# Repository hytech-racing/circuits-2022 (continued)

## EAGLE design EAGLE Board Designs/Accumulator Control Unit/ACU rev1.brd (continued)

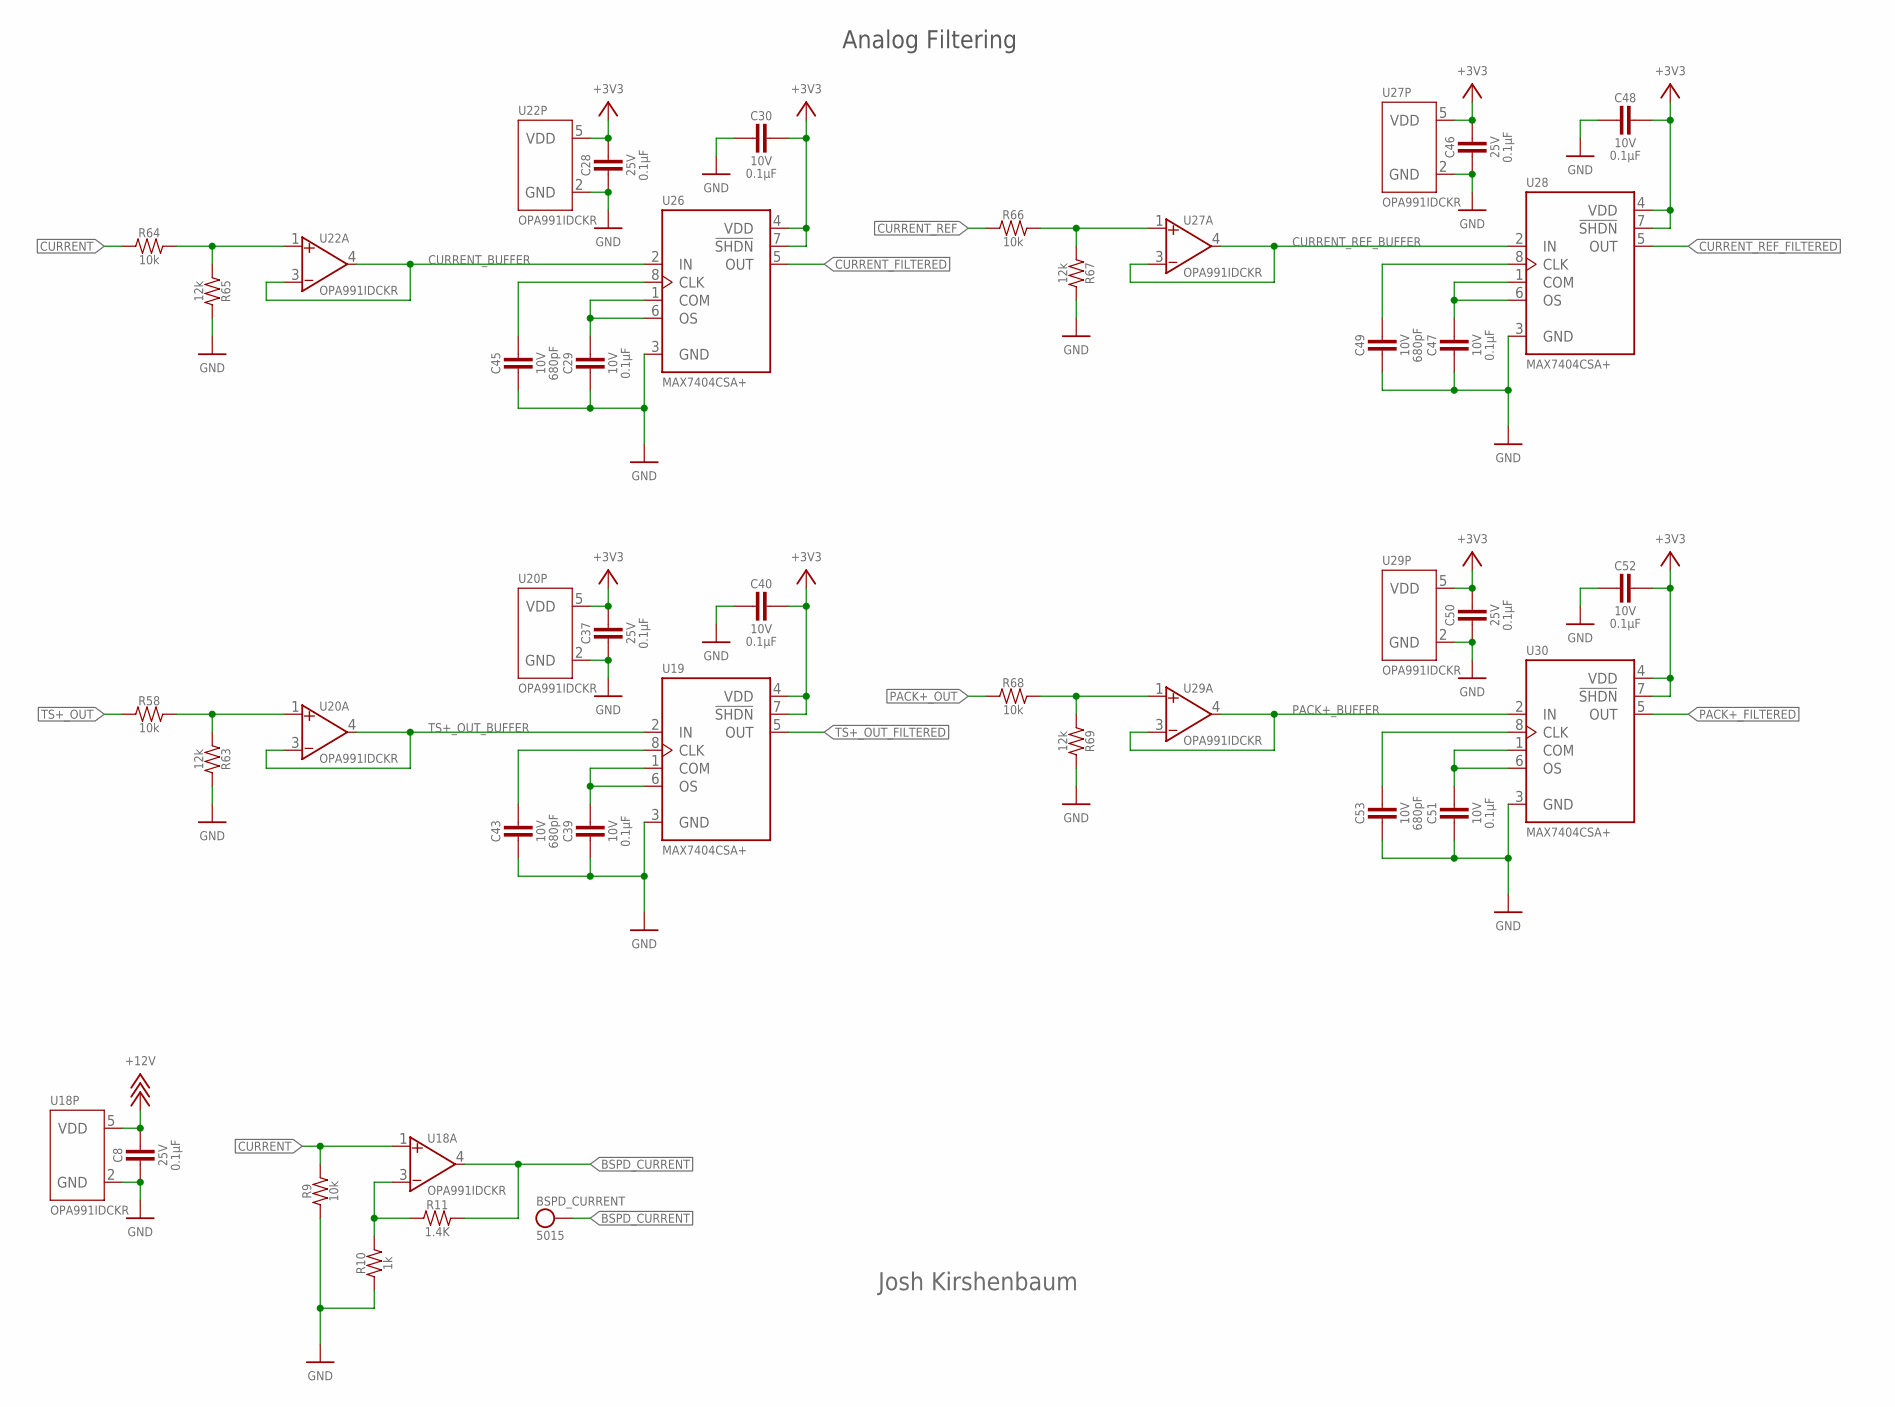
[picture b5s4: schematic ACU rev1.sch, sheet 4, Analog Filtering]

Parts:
BSPD_CURRENT: TEST_POINT; MICRO_MINIATURE
C8, C28, C37, C46, C50: CAPACITOR_0603_25V_0.1UF; 0603-CAP
C29, C30, C39, C40, C47, C48, C51, C52: CAPACITOR_0603_10V_0.1UF; 0603-CAP
C43, C45, C49, C53: CAPACITOR_0603_10V_680PF; 0603-CAP
R9, R58, R64, R66, R68: RESISTOR_0603_10K; 0603-RES
R10: RESISTOR_0603_1K; 0603-RES
R11: RESISTOR_0603_1.4K; 0603-RES
R63, R65, R67, R69: RESISTOR_0603_12K; 0603-RES
U18, U20, U22, U27, U29: OPAMP_1_CHANNEL_OPA991; SC-70-5
U19, U26, U28, U30: MAX7404; SOIC-08(NARROW,0.15")

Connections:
+3V3: C28.1, C30.1, C37.1, C40.1, C46.1, C48.1, C50.1, C52.1, U19.4 (VDD), U19.7 (!SHDN), U20.5 (VDD), U22.5 (VDD), U26.4 (VDD), U26.7 (!SHDN), U27.5 (VDD), U28.4 (VDD), U28.7 (!SHDN), U29.5 (VDD), U30.4 (VDD), U30.7 (!SHDN); also elsewhere on the board
+12V: C8.1, U18.5 (VDD); also elsewhere on the board
BSPD_CURRENT: BSPD_CURRENT.1, R11.2, U18.4 (VOUT); also elsewhere on the board
CURRENT: R9.2, R64.1, U18.1 (VIN+); also elsewhere on the board
CURRENT_BUFFER: U22.3 (VIN-), U22.4 (VOUT), U26.2 (IN)
CURRENT_FILTERED: U26.5 (OUT); also elsewhere on the board
CURRENT_REF: R66.1; also elsewhere on the board
CURRENT_REF_BUFFER: U27.3 (VIN-), U27.4 (VOUT), U28.2 (IN)
CURRENT_REF_FILTERED: U28.5 (OUT); also elsewhere on the board
GND: C8.2, C28.2, C29.2, C30.2, C37.2, C39.2, C40.2, C43.2, C45.2, C46.2, C47.2, C48.2, C49.2, C50.2, C51.2, C52.2, C53.2, R9.1, R10.1, R63.2, R65.2, R67.2, R69.2, U18.2 (GND), U19.3 (GND), U20.2 (GND), U22.2 (GND), U26.3 (GND), U27.2 (GND), U28.3 (GND), U29.2 (GND), U30.3 (GND); also elsewhere on the board
unnamed: R10.2, R11.1, U18.3 (VIN-)
unnamed: C39.1, U19.1 (COM), U19.6 (OS)
unnamed: C43.1, U19.8 (CLK)
unnamed: R58.2, R63.1, U20.1 (VIN+)
unnamed: C29.1, U26.1 (COM), U26.6 (OS)
unnamed: C45.1, U26.8 (CLK)
unnamed: R64.2, R65.1, U22.1 (VIN+)
unnamed: C47.1, U28.1 (COM), U28.6 (OS)
unnamed: C49.1, U28.8 (CLK)
unnamed: R66.2, R67.1, U27.1 (VIN+)
unnamed: C51.1, U30.1 (COM), U30.6 (OS)
unnamed: C53.1, U30.8 (CLK)
unnamed: R68.2, R69.1, U29.1 (VIN+)
PACK+_BUFFER: U29.3 (VIN-), U29.4 (VOUT), U30.2 (IN)
PACK+_FILTERED: U30.5 (OUT); also elsewhere on the board
PACK+_OUT: R68.1; also elsewhere on the board
TS+_OUT: R58.1; also elsewhere on the board
TS+_OUT_BUFFER: U19.2 (IN), U20.3 (VIN-), U20.4 (VOUT)
TS+_OUT_FILTERED: U19.5 (OUT); also elsewhere on the board

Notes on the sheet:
Josh Kirshenbaum
Analog Filtering

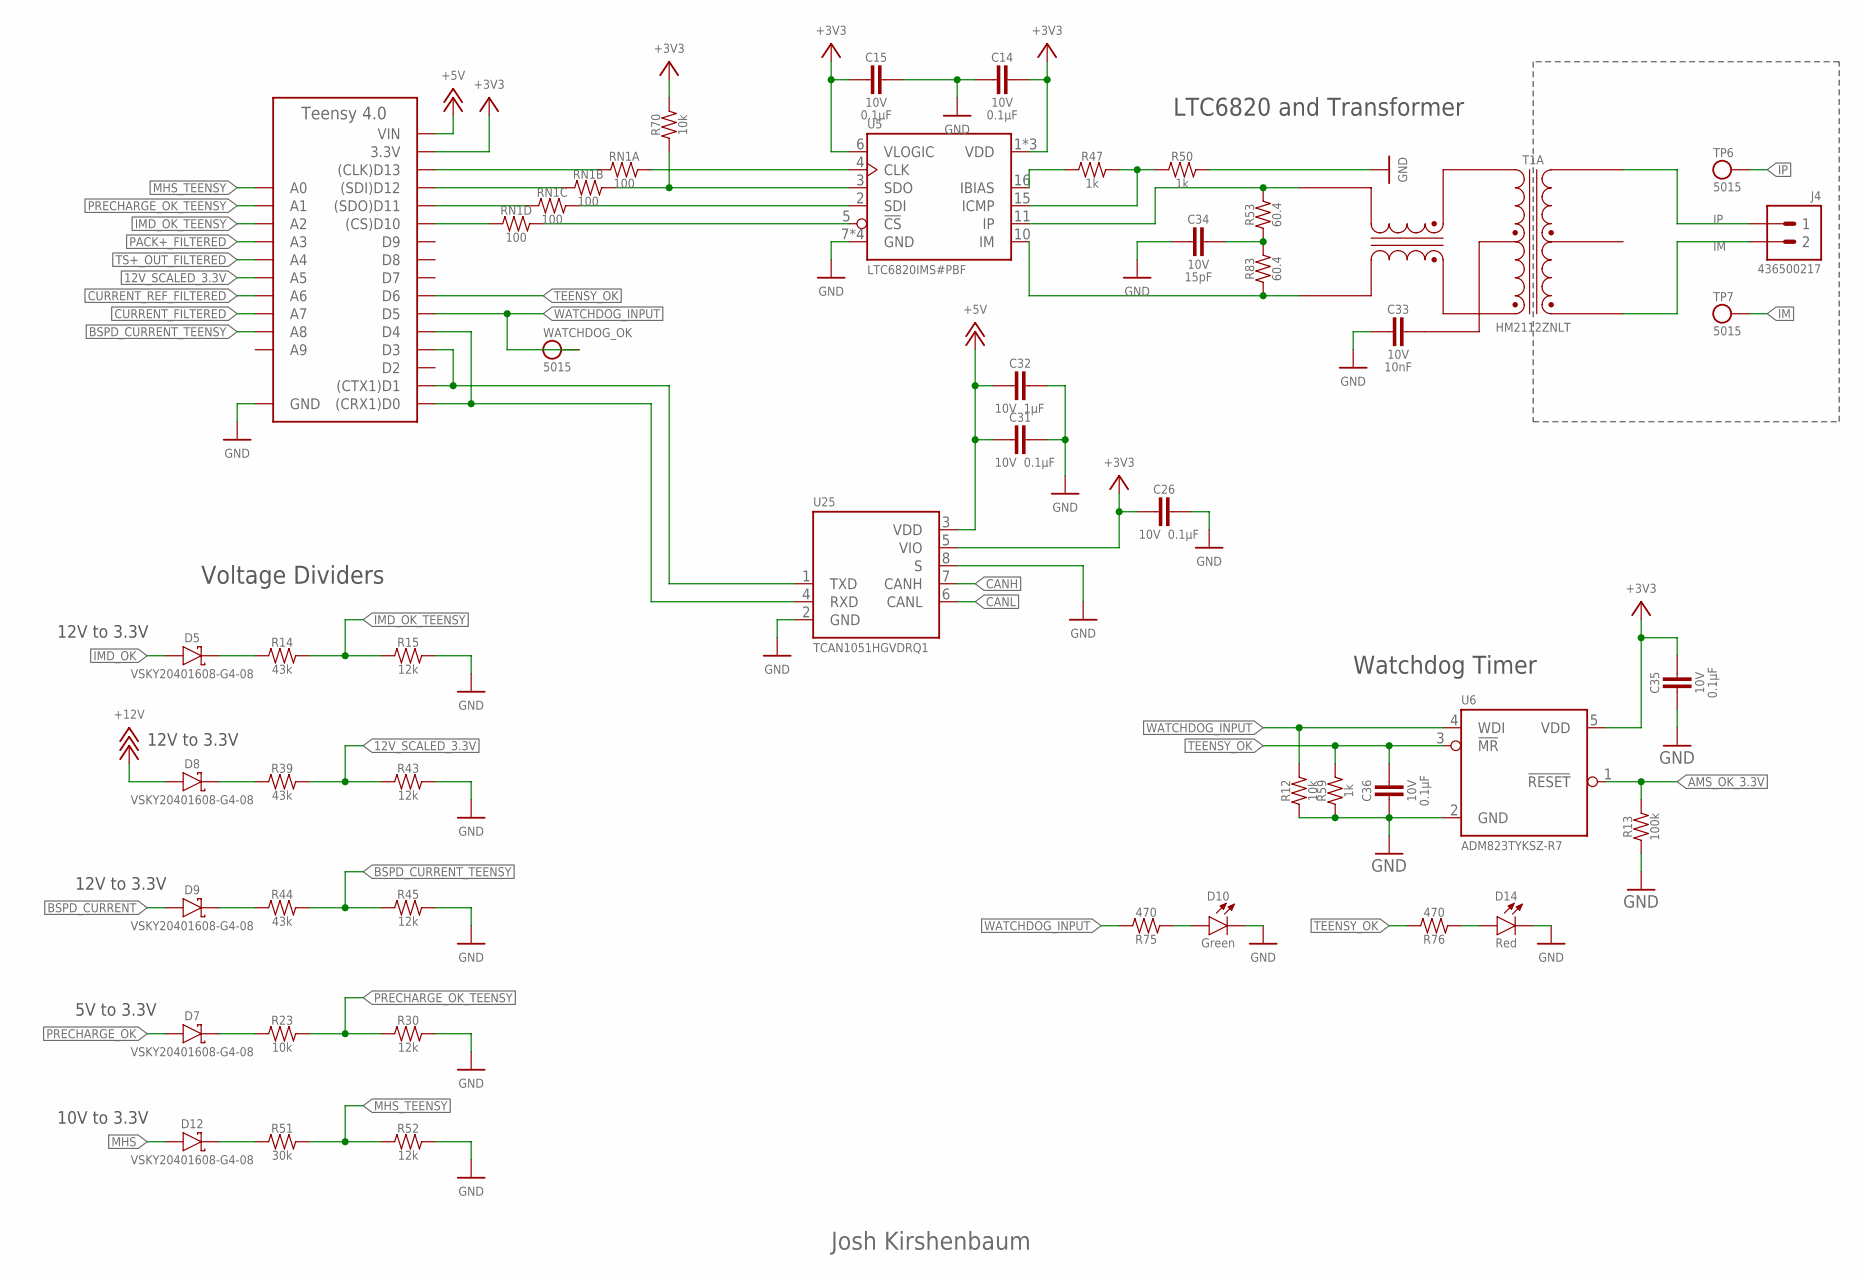
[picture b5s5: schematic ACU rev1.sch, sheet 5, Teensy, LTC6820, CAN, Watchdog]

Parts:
A1: TEENSY_4.0; TEENSY_SHORT
C14, C15, C26, C31, C35, C36: CAPACITOR_0603_10V_0.1UF; 0603-CAP
C32: CAPACITOR_0603_10V_1UF; 0603-CAP
C33: CAPACITOR_0603_10V_10NF; 0603-CAP
C34: CAPACITOR_0603_10V_15PF; 0603-CAP
D5, D7, D8, D9, D12: SCHOTTKY; CLP1608-2L
D10: LED_0603_GREEN; 0603-LED
D14: LED_0603_RED; 0603-LED
J4: CONNECTOR-2_MF_T_V_; MOLEX_MICROFIT_PTH_VERTICAL_02_SINGLE
R12, R23, R70: RESISTOR_0603_10K; 0603-RES
R13: RESISTOR_0603_100K; 0603-RES
R14, R39, R44: RESISTOR_0603_43K; 0603-RES
R15, R30, R43, R45, R52: RESISTOR_0603_12K; 0603-RES
R47, R50, R59: RESISTOR_0603_1K; 0603-RES
R51: RESISTOR_0603_30K; 0603-RES
R53, R83: RESISTOR_0603_60.4; 0603-RES
R75, R76: RESISTOR_0603_470; 0603-RES
RN1: RESISTOR_NETWORK_4_100; 1206-RES-ARRAY
T1: TRANSFORMER_HM2112ZNLT_AIRGAP; HM2112ZNLT_AIRGAP
TP6, TP7: TEST_POINT; MICRO_MINIATURE
U5: LTC6820; MSOP-16
U6: ADM823; SC-70-5
U25: TCAN1051HQV-Q1; SOIC-08(NARROW,0.15")
WATCHDOG_OK: TEST_POINT; MICRO_MINIATURE

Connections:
12V_SCALED_3.3V: A1.D19 (A5), R39.2, R43.1
+3V3: A1.3.3V, C14.1, C15.2, C26.2, C35.1, R70.2, U5.1 (VDD), U5.6 (VLOGIC), U5.9 (VDD), U5.12 (VDD), U6.5 (VDD), U25.5 (VIO); also elsewhere on the board
+5V: A1.VIN, C31.2, C32.2, U25.3 (VDD); also elsewhere on the board
+12V: D8.1 (A); also elsewhere on the board
AMS_OK_3.3V: R13.2, U6.1 (!RESET!); also elsewhere on the board
BSPD_CURRENT: D9.1 (A); also elsewhere on the board
BSPD_CURRENT_TEENSY: A1.D22 (A8), R44.2, R45.1
CANH: U25.7 (CANH); also elsewhere on the board
CANL: U25.6 (CANL); also elsewhere on the board
CS_LTC_6820: RN1.5 (2), U5.5 (!CS)
CURRENT_FILTERED: A1.D21 (A7); also elsewhere on the board
CURRENT_REF_FILTERED: A1.D20 (A6); also elsewhere on the board
GND: A1.AGND/GND (GND), A1.GND, C14.2, C15.1, C26.1, C31.1, C32.1, C33.2, C34.2, C35.2, C36.2, D10.1 (C), D14.1 (C), R12.1, R13.1, R15.2, R30.2, R43.2, R45.2, R50.2, R52.2, R59.1, U5.7 (GND), U5.8 (GND), U5.13 (GND), U5.14 (GND), U6.2 (GND), U25.2 (GND), U25.8 (S); also elsewhere on the board
IM: J4.2, T1.1 (MX+), TP7.1
IMD_OK: D5.1 (A); also elsewhere on the board
IMD_OK_TEENSY: A1.D16 (A2), R14.2, R15.1
IP: J4.1, T1.3 (MX-), TP6.1
MHS: D12.1 (A); also elsewhere on the board
MHS_TEENSY: A1.D14 (A0), R51.2, R52.1
unnamed: RN1.8 (2), U5.4 (CLK)
unnamed: R70.1, RN1.7 (2), U5.3 (SDO)
unnamed: RN1.6 (2), U5.2 (SDI)
unnamed: A1.D10 ((CS)D10), RN1.4 (1)
unnamed: A1.D11 ((SDO)D11), RN1.3 (1)
unnamed: A1.D0 ((CRX1)D0), A1.D4, U25.4 (RXD)
unnamed: A1.D1 ((CTX1)D1), A1.D3, U25.1 (TXD)
unnamed: D7.2 (C), R23.1
unnamed: D5.2 (C), R14.1
unnamed: D8.2 (C), R39.1
unnamed: D9.2 (C), R44.1
unnamed: R53.2, T1.10 (TD-), U5.11 (IP)
unnamed: R47.1, U5.16 (IBIAS)
unnamed: R47.2, R50.1, U5.15 (ICMP)
unnamed: R83.1, T1.12 (TD+), U5.10 (IM)
unnamed: C33.1, T1.11 (TCT)
unnamed: D12.2 (C), R51.1
unnamed: C34.1, R53.1, R83.2
unnamed: A1.D12 ((SDI)D12), RN1.2 (1)
unnamed: A1.D13 ((CLK)D13), RN1.1
unnamed: D10.2 (A), R75.1
unnamed: D14.2 (A), R76.1
PACK+_FILTERED: A1.D17 (A3); also elsewhere on the board
PRECHARGE_OK: D7.1 (A); also elsewhere on the board
PRECHARGE_OK_TEENSY: A1.D15 (A1), R23.2, R30.1
TEENSY_OK: A1.D6, C36.1, R59.2, R76.2, U6.3 (!MR!)
TS+_OUT_FILTERED: A1.D18 (A4); also elsewhere on the board
WATCHDOG_INPUT: A1.D5, R12.2, R75.2, U6.4 (WDI), WATCHDOG_OK.1

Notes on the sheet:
Josh Kirshenbaum
12V to 3.3V
5V to 3.3V
Watchdog Timer
Voltage Dividers
LTC6820 and Transformer
10V to 3.3V

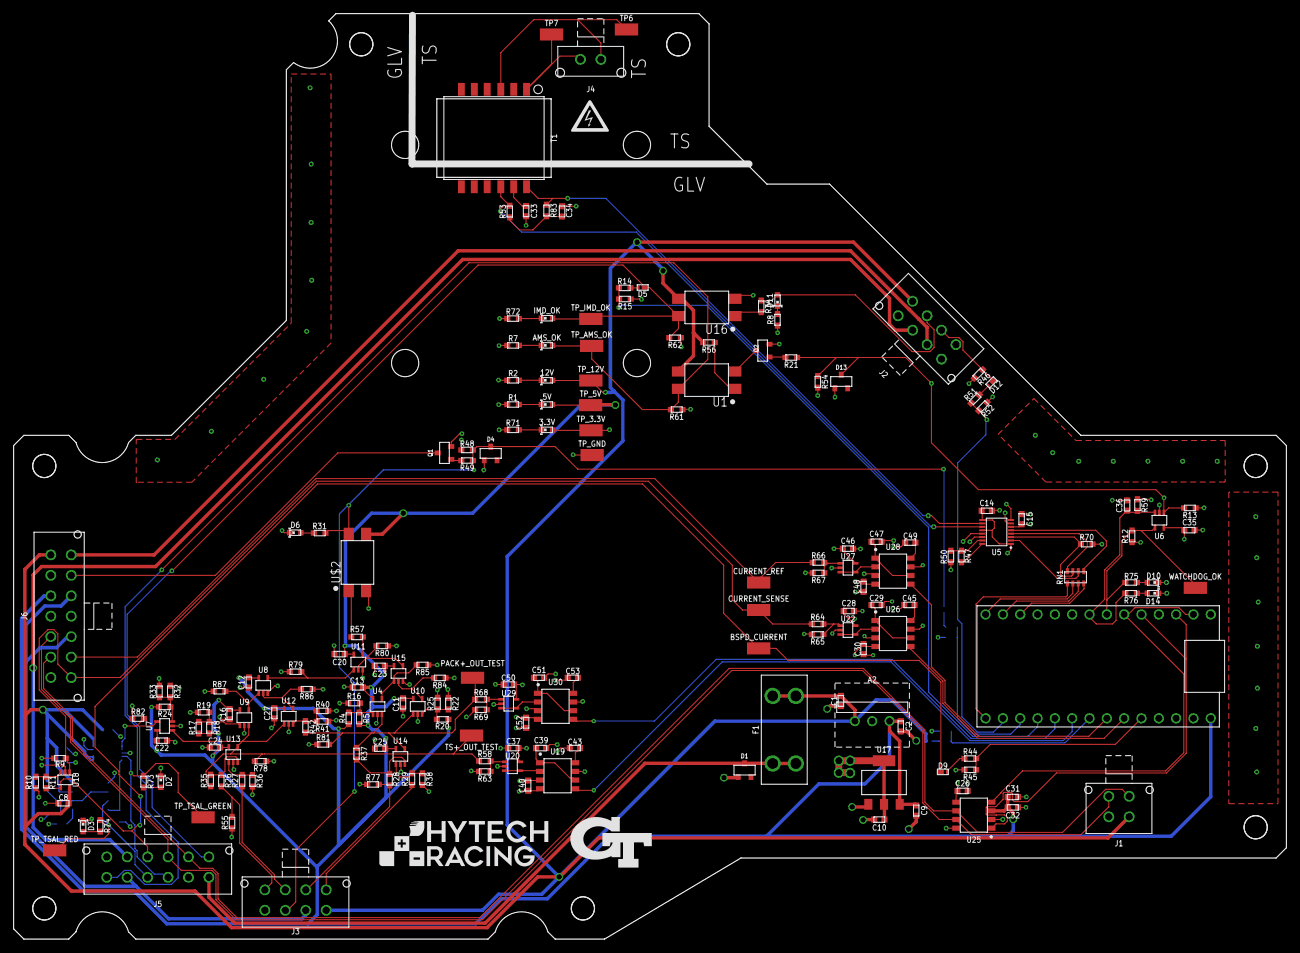
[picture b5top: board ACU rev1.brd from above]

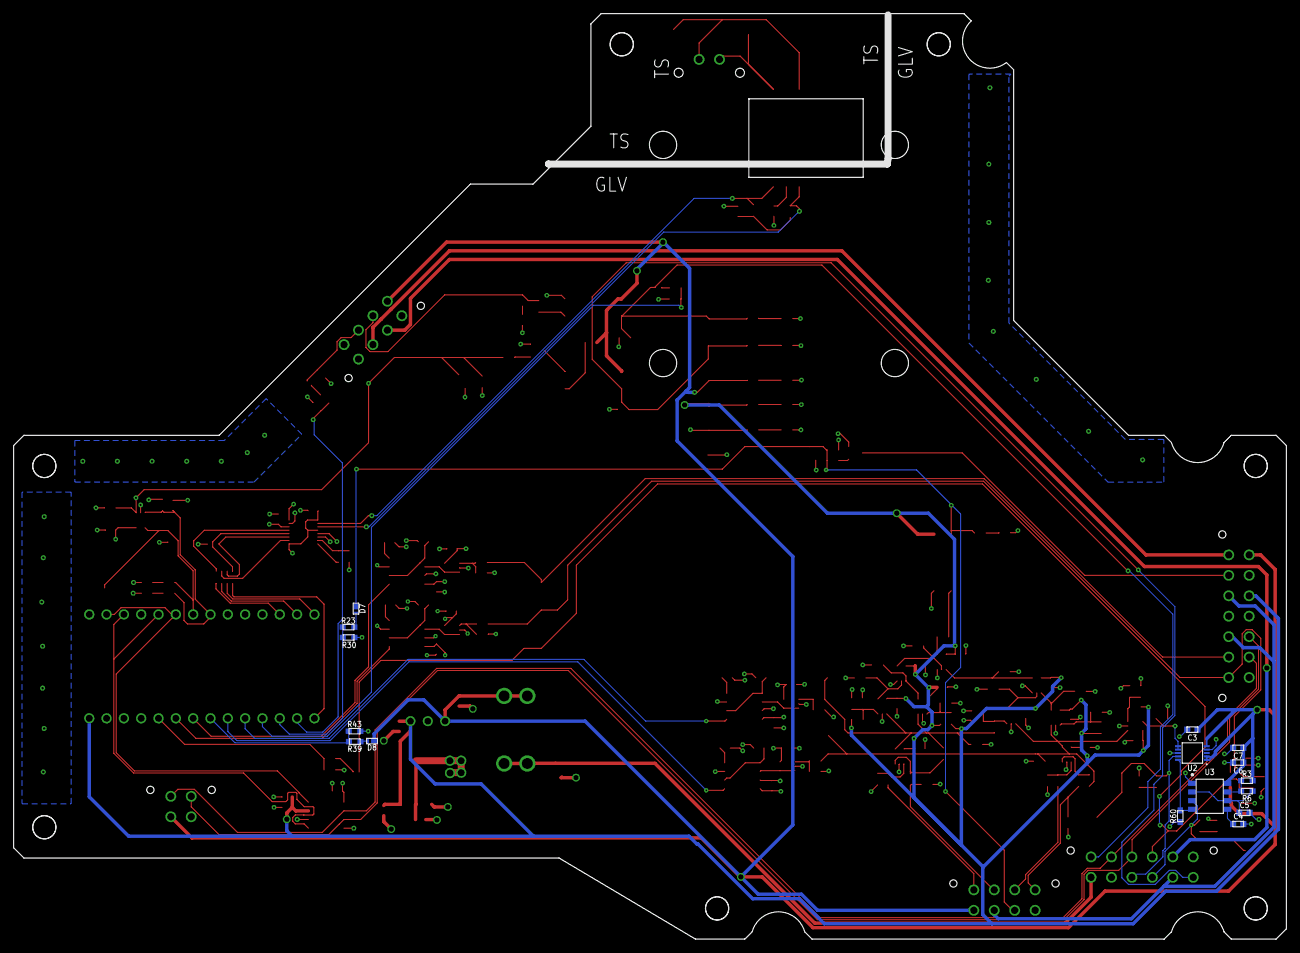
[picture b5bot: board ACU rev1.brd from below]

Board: 4 copper layers, 186.7 x 135.7 mm, 223 parts (16 on the bottom side), 117 nets.

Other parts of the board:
R84, R85, R86, R87: RESISTOR_0603_10K; 0603-RES
U$1, U$5: GLV
U$3, U$9, U$10: TS
U$4: HV_0.50"
U$6, U$7, U$8, U$11, U$12, U$13, U$14: MOUNTING_M3
U$15: LOGO_HYTECH_1.0"
U$16: LOGO_GT_0.50"

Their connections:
GND: R84.1, R85.1, R86.1, R87.1; also elsewhere on the board
PRECHARGE_REACHED: R86.2; also elsewhere on the board
TS+_OUT_OV_OK: R87.2; also elsewhere on the board
V_PACK_REF_OV_OK: R85.2; also elsewhere on the board
V_PACK_REF_UV_OK: R84.2; also elsewhere on the board

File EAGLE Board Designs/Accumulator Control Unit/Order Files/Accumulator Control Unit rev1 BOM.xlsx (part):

Qty | Value | Device | Package | Parts | Description | CAPACITANCE | COLOR | CURRENT | DKPN | MANUFACTURER | MOPN | MPN | POWER | RESET_VOLTAGE | RESISTANCE | TOLERANCE | VOLTAGE | VOLTAGE_CONTINUOUS | VOLTAGE_MAX | Column1
1 | ADG1423 | ADG1423 | MSOP-10 | U2 | ADG1423 Form-A/Form-C Analog Switch |  |  |  | ADG1423BRMZ-REEL7CT-ND | Analog Devices Inc. | 584-ADG1423BRMZ | ADG1423BRMZ
1 | ADM823 | ADM823 | SC-70-5 | U6 | ADM823 Watchdog |  |  |  | 505-ADM823TYKSZ-R7CT-ND | Analog Devices Inc. | 584-ADM823TYKSZ-R7 | ADM823TYKSZ-R7 |  | 3.08
24 | CAPACITOR_0603_10V_0.1UF | CAPACITOR_0603_10V_0.1UF | 0603-CAP | C11, C12, C13, C14, C15, C16, C20, C22, C23, C24, C25, C26, C27, C29, C30, C31,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 | Capacitor, Non-Polarized | 0.1µF |  |  | 720-1688-1-ND | Vishay Vitramon | 77-VJ0603Y104JXQPBC | VJ0603Y104JXQPW1BC |  |  |  | 0.05 | 10V
2 | CAPACITOR_0603_10V_10NF | CAPACITOR_0603_10V_10NF | 0603-CAP | C4, C33 | Capacitor, Non-Polarized | 10nF |  |  | 311-4054-1-ND | Yageo | 603-CC603KRX7R6BB103 | CC0603KRX7R6BB103 |  |  |  | 0.1 | 10V
1 | CAPACITOR_0603_10V_15PF | CAPACITOR_0603_10V_15PF | 0603-CAP | C34 | Capacitor, Non-Polarized | 15pF |  |  | 720-VJ0603A150FXQPW1BCCT-ND | Vishay Vitramon | 77-VJ0603A150FXQPBC | VJ0603A150FXQPW1BC |  |  |  | 0.01 | 10V
2 | CAPACITOR_0603_10V_1UF | CAPACITOR_0603_10V_1UF | 0603-CAP | C9, C32 | Capacitor, Non-Polarized | 1µF |  |  | 311-1796-1-ND | Yageo | 603-CC603KRX7R6BB105 | CC0603KRX7R6BB105 |  |  |  | 0.1 | 10V
2 | CAPACITOR_0603_10V_4.7UF | CAPACITOR_0603_10V_4.7UF | 0603-CAP | C5, C10 | Capacitor, Non-Polarized | 4.7µF |  |  | 1276-1044-1-ND | Samsung Electro-Mechanics | 187-CL10A475KP8NNNC | CL10A475KP8NNNC |  |  |  | 0.1 | 10V
4 | CAPACITOR_0603_10V_680PF | CAPACITOR_0603_10V_680PF | 0603-CAP | C43, C45, C49, C53 | Capacitor, Non-Polarized | 680pF |  |  | 732-7757-1-ND | Würth Elektronik | 710-885012006013 | 885012006013 |  |  |  | 0.05 | 10V
6 | CAPACITOR_0603_25V_0.1UF | CAPACITOR_0603_25V_0.1UF | 0603-CAP | C7, C8, C28, C37, C46, C50 | Capacitor, Non-Polarized | 0.1µF |  |  | 1276-1006-1-ND | Samsung Electro-Mechanics | 187-CL10B104KA8NNNC | CL10B104KA8NNNC |  |  |  | 0.1 | 25V
2 | CAPACITOR_0603_25V_10UF | CAPACITOR_0603_25V_10UF | 0603-CAP | C1, C2 | Capacitor, Non-Polarized | 10µF |  |  | 490-7202-1-ND | Murata Electronics | 81-GRM188R61E106MA3D | GRM188R61E106MA73D |  |  |  | 0.2 | 25V
2 | CAPACITOR_0603_25V_1UF | CAPACITOR_0603_25V_1UF | 0603-CAP | C3, C6 | Capacitor, Non-Polarized | 1µF |  |  | 1276-1184-1-ND | Samsung Electro-Mechanics | 187-CL10B105KA8NNNC | CL10B105KA8NNNC |  |  |  | 0.1 | 25V
1 | CONNECTOR-12_MF_T_V_ | CONNECTOR-12_MF_T_V_ | MOLEX_MICROFIT_PTH_VERTICAL_12_DUAL | J5 | 12 pin connector |  |  |  |  | MOLEX |  | 430451214
1 | CONNECTOR-14_MF_T_V_ | CONNECTOR-14_MF_T_V_ | MOLEX_MICROFIT_PTH_VERTICAL_14_DUAL | J6 | 14 pin connector |  |  |  |  | MOLEX |  | 430451414
1 | CONNECTOR-2_MF_T_V_ | CONNECTOR-2_MF_T_V_ | MOLEX_MICROFIT_PTH_VERTICAL_02_SINGLE | J4 | 2 Pin Connector |  |  |  |  | MOLEX |  | 436500217
2 | CONNECTOR-8_MF_T_V_ | CONNECTOR-8_MF_T_V_ | MOLEX_MICROFIT_PTH_VERTICAL_08_DUAL | J2, J3 | 8 Pin Connector |  |  |  |  | MOLEX |  | 430450814
1 | CONNECTOR-CAN_MF_T_V_ | CONNECTOR-CAN_MF_T_V_ | MOLEX_MICROFIT_PTH_VERTICAL_04_DUAL | J1 | HyTech CAN Connector |  |  |  |  | Molex |  | 430450414
1 | FUSE_MINI-BLADE_1A | FUSE_MINI-BLADE_1A | MINI-BLADE_FUSE_HOLDER | F1 | Fuse |  |  | 1A
1 | LED_0603_BLUE | LED_0603_BLUE | 0603-LED | 5V | LED |  | Blue |  | 754-1789-1-ND | Kingbright | 604-APT1608VBC/D | APT1608VBC/D
4 | LED_0603_GREEN | LED_0603_GREEN | 0603-LED | 3.3V, AMS_OK, D2, D10 | LED |  | Green |  | 754-1790-1-ND | Kingbright | 604-APT1608ZGCK | APT1608ZGCK
1 | LED_0603_ORANGE | LED_0603_ORANGE | 0603-LED | IMD_OK | LED |  | Orange |  | 754-1120-1-ND | Kingbright | 604-APT1608SECK | APT1608SECK
4 | LED_0603_RED | LED_0603_RED | 0603-LED | 12V, D3, D6, D14 | LED |  | Red |  | 754-1786-1-ND | Kingbright | 604-APT1608SECKJ3PRV | APT1608SECK/J3-PRV
1 | LED_0603_YELLOW | LED_0603_YELLOW | 0603-LED | D11 | LED |  | Yellow |  | 754-1788-1-ND | Kingbright | 604-APT1608SYCK/J3-PRV | APT1608SYCK/J3-PRV
1 | LM555 | LM555 | SOIC-08(NARROW,0.15)" | U3 | **555 Precision Timer |  |  |  | LM555CMX/NOPBCT-ND | Texas Instruments | 926-LM555CMX/NOPB | LM555CMX/NOPB
3 | LOGICGATE_AND_DCK3 | LOGICGATE_AND_DCK3 | SC-70-5 | U8, U11, U15 | AND Gate |  |  |  | 296-SN74LVC1G08DCK3TR-ND | Texas Instruments | 595-SN74LVC1G08DCK3 | SN74LVC1G08DCK3
1 | LTC6820 | LTC6820 | MSOP-16 | U5 | LTC6820 isoSPI Isolated Communications Interface |  |  |  |  | Analog Devices |  | LTC6820IMS#PBF
4 | MAX7404 | MAX7404 | SOIC-08(NARROW,0.15)" | U19, U26, U28, U30 | 8th-Order Maxim Filter |  |  |  | MAX7404CSA+-ND | Maxim Integrated | 700-MAX7404CSA | MAX7404CSA+
12 | OPAMP_1_CHANNEL_OPA991 | OPAMP_1_CHANNEL_OPA991 | SC-70-5 | U4, U7, U9, U10, U12, U13, U14, U18, U20, U22, U27, U29 | Op-Amp 1 Channel |  |  |  | 296-OPA991IDCKRCT-ND | Texas Instruments | 595-OPA991IDCKR | OPA991IDCKR
3 | RELAY_SOLIDSTATE_NO | RELAY_SOLIDSTATE_NO | DIP-4 | U$2, U1, U16 | AQY214EH Normally Open Solid State Relay |  |  |  |  |  |  | AQY214EHA
1 | RESISTOR_0603_1.4K | RESISTOR_0603_1.4K | 0603-RES | R11 | Resistor |  |  |  | 311-2465-1-ND | Yageo | 603-RT0603DRE071K4L | RT0603DRE071K4L | 0.1W |  | 1.4K | 5.0000000000000001E-3 |  | 75V | 75V
2 | RESISTOR_0603_10 | RESISTOR_0603_10 | 0603-RES | R21, R49 | Resistor |  |  |  | 311-10.0HRCT-ND | Yageo | 603-RC0603FR-0710RL | RC0603FR-0710RL | 0.1W |  | 10 | 0.01 |  | 1V | 75V
2 | RESISTOR_0603_10.2K | RESISTOR_0603_10.2K | 0603-RES | R16, R19 | Resistor |  |  |  | P10.2KDBCT-ND | Panasonic Electronic Components | 667-ERA-3AEB1022V | ERA-3AEB1022V | 0.1W |  | 10.2k | 1E-3 |  | 31.94V | 75V
4 | RESISTOR_0603_10.5K | RESISTOR_0603_10.5K | 0603-RES | R35, R36, R37, R38 | Resistor |  |  |  | P10.5KDBCT-ND | Panasonic Electronic Components | 677-ERA-3AEB1052V | ERA-3AEB1052V | 0.1W |  | 10.5k | 1E-3 |  | 32.40V | 75V
1 | RESISTOR_0603_100K | RESISTOR_0603_100K | 0603-RES | R13 | Resistor |  |  |  | YAG2294CT-ND | Yageo | 603-RC0603JR-10100KL | RC0603JR-10100KL | 0.1W |  | 100k | 0.05 |  | 75V | 75V
23 | RESISTOR_0603_10K | RESISTOR_0603_10K | 0603-RES | R9, R12, R23, R48, R54, R55, R58, R60, R61, R62, R64, R66, R68, R77, R78, R79, 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 | Resistor |  |  |  | 311-10.0KHRCT-ND | Yageo | 603-RC0603FR-0710KL | RC0603FR-0710KL | 0.1W |  | 10k | 0.01 |  | 31.62V | 75V
1 | RESISTOR_0603_11.3K | RESISTOR_0603_11.3K | 0603-RES | R42 | Resistor |  |  |  | P11.3KDBCT-ND | Panasonic Electronic Components | 667-ERA-3AEB1132V | ERA-3AEB1132V | 0.1W |  | 11.3k | 1E-3 |  | 33.62V | 75V
7 | RESISTOR_0603_11.5K | RESISTOR_0603_11.5K | 0603-RES | R20, R25, R26, R27, R28, R29, R33 | Resistor |  |  |  | P11.5KDBCT-ND | Panasonic Electronic Components | 667-ERA-3AEB1152V | ERA-3AEB1152V | 0.1W |  | 11.5k | 1E-3 |  | 33.91V | 75V
9 | RESISTOR_0603_12K | RESISTOR_0603_12K | 0603-RES | R15, R30, R43, R45, R52, R63, R65, R67, R69 | Resistor |  |  |  | 311-12.0KHRCT-ND | Yageo | 603-RC0603FR-0712KL | RC0603FR-0712KL | 0.1W |  | 12k | 0.01 |  | 34.64V | 75V
12 | RESISTOR_0603_1K | RESISTOR_0603_1K | 0603-RES | R1, R2, R3, R7, R8, R10, R31, R47, R50, R59, R70, R71 | Resistor |  |  |  | 311-1.00KHRCT-ND | Yageo | 603-RC0603FR-071KL | RC0603FR-071KL | 0.1W |  | 1k | 0.01 |  | 10.00V | 75V
1 | RESISTOR_0603_2.2K | RESISTOR_0603_2.2K | 0603-RES | R46 | Resistor |  |  |  | 13-RC0603DR-072K2LCT-ND | Yageo | 603-RC0603DR-072K2L | RC0603DR-072K2L | 0.1W |  | 2.2k | 5.0000000000000001E-3 |  | 75V | 75V
1 | RESISTOR_0603_215K | RESISTOR_0603_215K | 0603-RES | R41 | Resistor |  |  |  | P215KDBCT-ND | Panasonic Electronic Components | 667-ERA-3AEB2153V | ERA-3AEB2153V | 0.1W |  | 215k | 1E-3 |  | 75V | 75V
5 | RESISTOR_0603_2K | RESISTOR_0603_2K | 0603-RES | R34, R56, R72, R73, R74 | Resistor |  |  |  | P2.0KBDCT-ND | Panasonic Electronic Components | 667-ERA-3ARB202V | ERA-3ARB202V | 0.1W |  | 2k | 1E-3 |  | 14.14V | 75V
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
